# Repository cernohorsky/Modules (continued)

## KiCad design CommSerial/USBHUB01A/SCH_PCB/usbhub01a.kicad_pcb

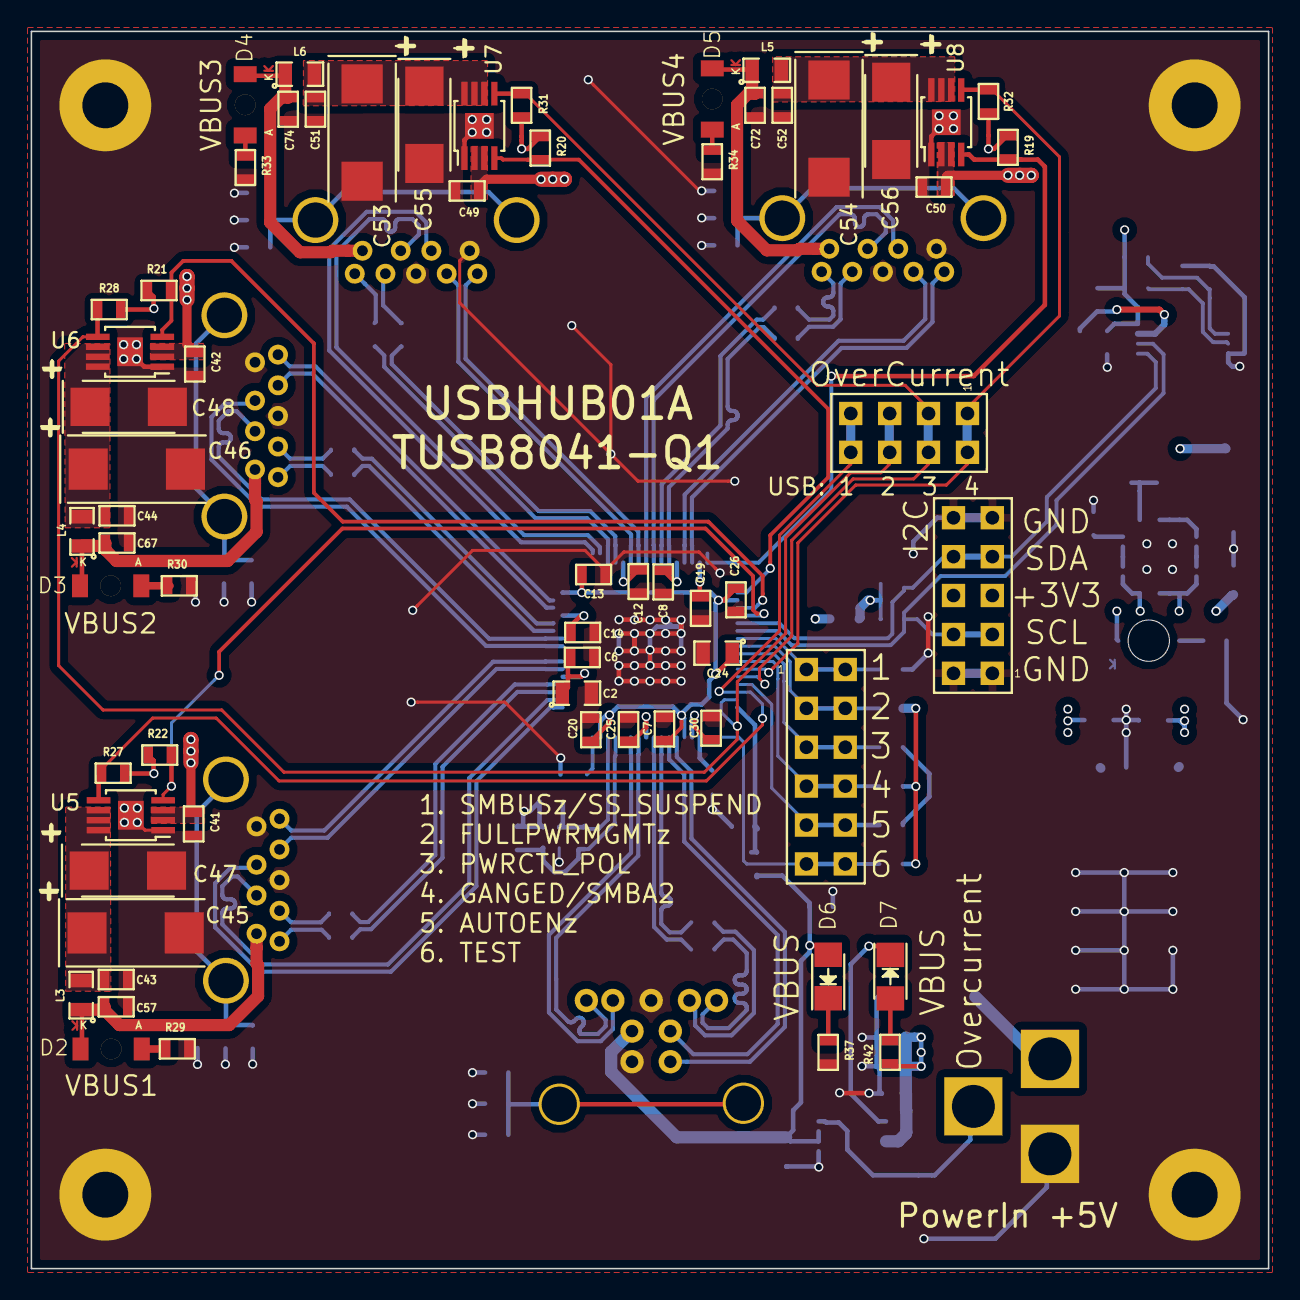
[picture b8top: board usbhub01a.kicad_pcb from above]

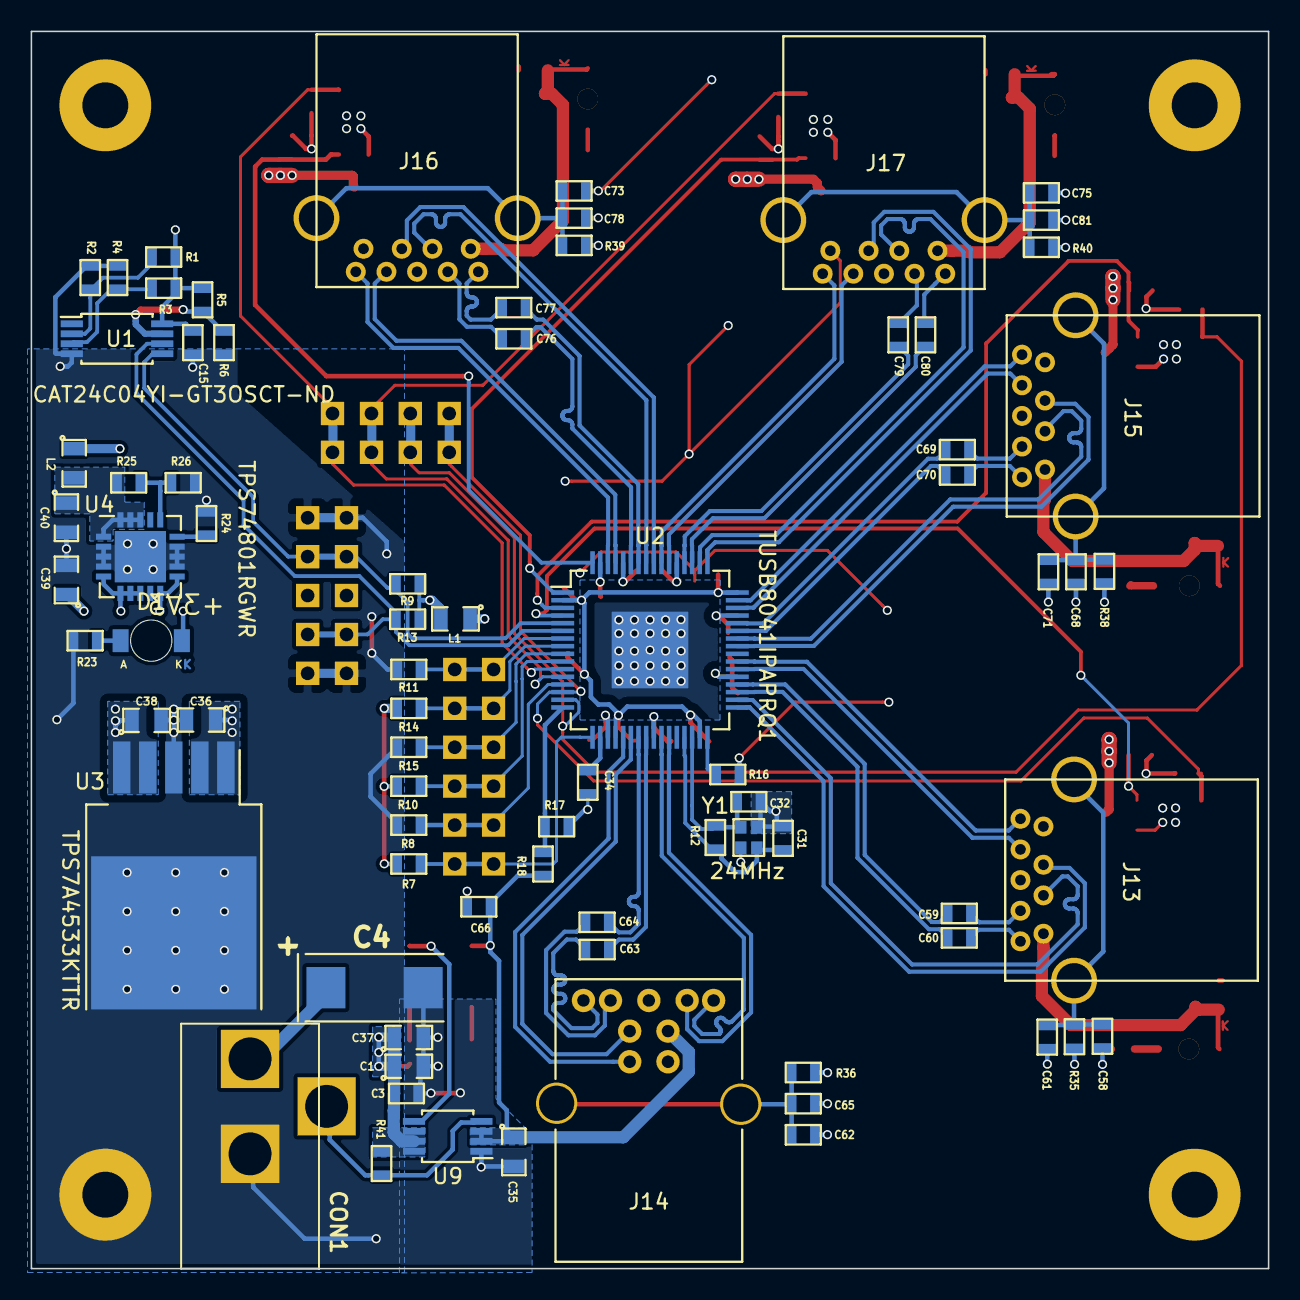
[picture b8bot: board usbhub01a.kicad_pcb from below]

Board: 4 copper layers, 80.8 x 80.8 mm, 145 parts (77 on the bottom side), 95 nets.

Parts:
C1, C2, C24, C36, C37, C38, C39, C40: 10uF; SMD-0805
C3, C6, C7, C8, C12, C13, C14, C15, C19, C20, C25, C26, C30, C41, C42, C43, C44, C49, C50, C51, C52, C57, C58, C59, C60, C62, C63, C64, C67, C68, C69, C70, C72, C73, C74, C75, C76, C77, C79, C80: 100nF; SMD-0603
C4, C45, C46, C53, C54: 100uF; TantalC_SizeD_Reflow
C31, C32: 18pF; SMD-0603
C34: 1uF; SMD-0603
C35: 1uF; SMD-0805
C47, C48, C55, C56: 47uF; TantalC_SizeC_Reflow
C61, C71, C78, C81: 1nF; SMD-0603
C65: 1nF 2kV; SMD-0603
C66: 10uF; SMD-0603
CON1: PowerIn +5V; DC2,1MM
D1: +3V3; LED_1206
D2: VBUS1; LED_1206
D3: VBUS2; LED_1206
D4: VBUS3; LED_1206
D5: VBUS4; LED_1206
D6: VBUS-UP; LED_1206
D7: LED; LED_1206
J1: OverCurrent; Straight_2x04
J2: Test & Misc Signals; Straight_2x06
J12: I2C; Straight_2x05
J13, J15, J16, J17: USB3_A; USB3_0_A
J14: USB3_B; USB3_0_B
L1, L2, L3, L4, L5, L6: BLM21PG300SN1D; SMD-0805
M1, M2, M3, M4: HOLE; MountingHole_3mm
R1, R3, R24: -; SMD-0603
R2, R4, R6: 1k; SMD-0603
R5: NOPOP; SMD-0603
R7, R8, R10, R11, R14, R15, R19, R20, R21, R22: 4K7; SMD-0603
R9, R13, R17, R41: 10k; SMD-0603
R12, R35, R36, R38, R39, R40: 1M; SMD-0603
R16: 9k53; SMD-0603
R18: 90k9; SMD-0603
R23, R26, R29, R30, R33, R34, R37: 330R; SMD-0603
R25: 1K87; SMD-0603
R27, R28, R31, R32: 10K; SMD-0603
R42: 470R; SMD-0603
U1: CAT24C04YI-GT3OSCT-ND; TSSOP-8_4.4x3mm_Pitch0.65mm
U2: TUSB8041IPAPRQ1; HTQFP-64_10x10mm_Pitch0.5mm
U3: TPS7A4533KTTR; TO-263-5
U4: TPS74801RGWR; QFN-20-1EP_5x5mm_Pitch0.65mm
U5, U6, U7, U8: TPS2001CDGN; MSOP-8-1EP_3x3mm_Pitch0.65mm
U9: AP22811; MSOP-8_3x3mm_Pitch0.65mm
Y1: 24MHz; NX2016HA

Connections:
+1V1: C40.1, L2.2, R25.1, U4.1, U4.18, U4.19, U4.20
+3V3: C15.1, C38.1, C39.1, D1.1, J12.5, J12.6, L1.2, R1.1, R3.1, R5.1, R7.1, R9.1, R10.1, R13.1, R14.1, R19.1, R20.1, R21.1, R22.1, R27.1, R28.1, R31.1, R32.1, U1.8, U3.4, U3.5, U4.5, U4.6, U4.7, U4.8, U4.10, U4.11
+5V: C1.1, C3.1, C4.1, C36.1, C37.1, C41.1, C42.1, C49.1, C50.1, CON1.1, R41.1, R42.1, U3.1, U3.2, U5.2, U5.3, U6.2, U6.3, U7.2, U7.3, U8.2, U8.3, U9.6, U9.7, U9.8
/AUTOENZ_HS_SUS: J2.9, J2.10, R8.1, U2.13
/DN1_VBUS: C43.1, C45.1, C47.1, L3.2, U5.6, U5.7, U5.8
/DN2_VBUS: C44.1, C46.1, C48.1, L4.2, U6.6, U6.7, U6.8
/DN3_VBUS: C51.1, C53.1, C55.1, L6.2, U7.6, U7.7, U7.8
/DN4_VBUS: C52.1, C54.1, C56.1, L5.2, U8.6, U8.7, U8.8
/FULLPWRMGMTZ_SMBA1: J2.3, J2.4, R14.2, U2.8
/GANGED_SMBA2_SH_UP: J2.7, J2.8, R10.2, U2.10
/IO1V1: C2.1, C6.1, C8.1, C12.1, C14.1, C19.1, C25.1, C30.1, L2.1, U2.19, U2.25, U2.37, U2.45, U2.53, U2.60, U2.63
/IO3V3: C7.1, C13.1, C20.1, C24.1, C26.1, L1.1, U2.2, U2.20, U2.31, U2.48
/OVERCUR1Z_TDI: J1.7, J1.8, R27.2, U2.14, U5.5
/OVERCUR2Z_TMS: J1.5, J1.6, R28.2, U2.15, U6.5
/OVERCUR3Z_TCK: J1.3, J1.4, R31.2, U2.12, U7.5
/OVERCUR4Z: J1.1, J1.2, R32.2, U2.11, U8.5
/PWRCTL_POL_TDO: J2.5, J2.6, R15.1, U2.9
/PWRON1_BATEN1: R22.2, U2.4, U5.4
/PWRON2_BATEN2: R21.2, U2.3, U6.4
/PWRON3_BATEN3: R20.2, U2.1, U7.4
/PWRON4_BATEN4: R19.2, U2.64, U8.4
/SCL: J12.3, J12.4, R13.2, U1.6, U2.6
/SDA: J12.7, J12.8, R9.2, U1.5, U2.5
/SMBUSZ_SS_SUS: J2.1, J2.2, R11.1, U2.7
/TEST_TRSTZ: J2.11, J2.12, R7.2, U2.17
/USBPORT/DN1+: C59.2, J13.8
/USBPORT/DN1-: C60.2, J13.9
/USBPORT/DN2+: C69.2, J15.8
/USBPORT/DN2-: C70.2, J15.9
/USBPORT/DN3+: C79.2, J17.8
/USBPORT/DN3-: C80.2, J17.9
/USBPORT/DN4+: C76.2, J16.8
/USBPORT/DN4-: C77.2, J16.9
/USBPORT/SSTX_N: C63.2, J14.5
/USBPORT/SSTX_P: C64.2, J14.6
/USB_DM_DN1+: J13.3, U2.33
/USB_DM_DN1-: J13.2, U2.34
/USB_DM_DN2+: J15.3, U2.41
/USB_DM_DN2-: J15.2, U2.42
/USB_DM_DN3+: J17.3, U2.49
/USB_DM_DN3-: J17.2, U2.50
/USB_DM_DN4+: J16.3, U2.56
/USB_DM_DN4-: J16.2, U2.57
/USB_DM_UP+: J14.3, U2.21
/USB_DM_UP-: J14.2, U2.22
/USB_SSRXM_DN1+: J13.6, U2.38
/USB_SSRXM_DN1-: J13.5, U2.39
/USB_SSRXM_DN2+: J15.6, U2.46
/USB_SSRXM_DN2-: J15.5, U2.47
/USB_SSRXM_DN3+: J17.6, U2.54
/USB_SSRXM_DN3-: J17.5, U2.55
/USB_SSRXM_DN4+: J16.6, U2.61
/USB_SSRXM_DN4-: J16.5, U2.62
/USB_SSRXM_UP+: J14.9, U2.26
/USB_SSRXM_UP-: J14.8, U2.27
/USB_SSTXM_DN1+: C60.1, U2.35
/USB_SSTXM_DN1-: C59.1, U2.36
/USB_SSTXM_DN2+: C70.1, U2.43
/USB_SSTXM_DN2-: C69.1, U2.44
/USB_SSTXM_DN3+: C80.1, U2.51
/USB_SSTXM_DN3-: C79.1, U2.52
/USB_SSTXM_DN4+: C77.1, U2.58
/USB_SSTXM_DN4-: C76.1, U2.59
/USB_SSTXM_UP+: C64.1, U2.23
/USB_SSTXM_UP-: C63.1, U2.24
/USB_VBUS_UP: C35.1, C66.1, D6.2, J14.1, R18.1, U9.2, U9.3
/VBUS1: C57.1, D2.2, J13.1, L3.1
/VBUS2: C67.1, D3.2, J15.1, L4.1
/VBUS3: C74.1, D4.2, J17.1, L6.1
/VBUS4: C72.1, D5.2, J16.1, L5.1
GND: C1.2, C2.2, C3.2, C4.2, C6.2, C7.2, C8.2, C12.2, C13.2, C14.2, C15.2, C19.2, C20.2, C24.2, C25.2, C26.2, C30.2, C31.2, C32.2, C34.2, C35.2, C36.2, C37.2, C38.2, C39.2, C40.2, C41.2, C42.2, C43.2, C44.2, C45.2, C46.2, C47.2, C48.2, C49.2, C50.2, C51.2, C52.2, C53.2, C54.2, C55.2, C56.2, C57.2, C58.2, C61.2, C62.2, C65.2, C66.2, C67.2, C68.2, C71.2, C72.2, C73.2, C74.2, C75.2, C78.2, C81.2, CON1.2, J12.1, J12.2, J12.9, J12.10, J13.4, J13.7, J14.4, J14.7, J15.4, J15.7, J16.4, J16.7, J17.4, J17.7, M1.1, M2.1, M3.1, M4.1, R2.2, R4.2, R6.2, R8.2, R11.2, R15.2, R16.2, R17.2, R23.2, R24.2, R26.2, R29.2, R30.2, R33.2, R34.2, R35.2, R36.2, R37.2, R38.2, R39.2, R40.2, U1.4, U2.65, U3.3, U4.2, U4.3, U4.4, U4.12, U4.13, U4.14, U4.21, U5.1, U5.9, U6.1, U6.9, U7.1, U7.9, U8.1, U8.9, U9.1, Y1.2, Y1.4
unnamed: C31.1, R12.2, U2.29, Y1.3
unnamed: C32.1, R12.1, U2.30, Y1.1
unnamed: C34.1, U2.18
unnamed: C58.1, C61.1, J13.10, R35.1
unnamed: C62.1, C65.1, J14.10, R36.1
unnamed: C68.1, C71.1, J15.10, R38.1
unnamed: C73.1, C78.1, J16.10, R39.1
unnamed: C75.1, C81.1, J17.10, R40.1
unnamed: CON1.3, R41.2, U9.4
unnamed: D1.2, R23.1
unnamed: D2.1, R29.1
unnamed: D3.1, R30.1
unnamed: D4.1, R33.1
unnamed: D5.1, R34.1
unnamed: D6.1, R37.1
unnamed: D7.1, U9.5
unnamed: D7.2, R42.2
unnamed: R1.2, R2.1, U1.2
unnamed: R3.2, R4.1, U1.3
unnamed: R5.2, R6.1, U1.7
unnamed: R16.1, U2.32
unnamed: R17.1, R18.2, U2.16
unnamed: R24.1, U4.15
unnamed: R25.2, R26.1, U4.16

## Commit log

2017-08-21 Vyhozený vypínač, přidaný "Distribution Load Switch"
2017-08-21 Přidání tantalového kondenzátoru na +5V větev
2018-01-28 NFC-Reader
2018-01-28 SPI-Expander
2018-01-28 NFC_Reader
2018-01-28 USB-Hub-funkcni finalni verze
2018-01-28 LoRa-node-PCB-antenna
2018-01-28 LM5104-PrvniVerze
2018-01-28 BTT60500-PrvniVerze
2018-01-28 LMR14050-PrvniVerze
2018-05-24 Add files via upload
    add ATmega328P, MCP73871, TPS63031, finished layout rev. 0
2018-06-07 Prvni vykop
2018-06-08 LM3478
2018-06-08 LM3478, ESP8266 layout
2018-06-09 ESP8266, TPS63030 - Final
2018-06-09 TUSB8041IPAPRQ1 - Final - Verified design
2018-06-12 Nixie layout
2018-06-13 Power supplies layout
2018-06-16 Final
